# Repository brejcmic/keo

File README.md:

# B0B13KEO

- materiály, 
- prezentace

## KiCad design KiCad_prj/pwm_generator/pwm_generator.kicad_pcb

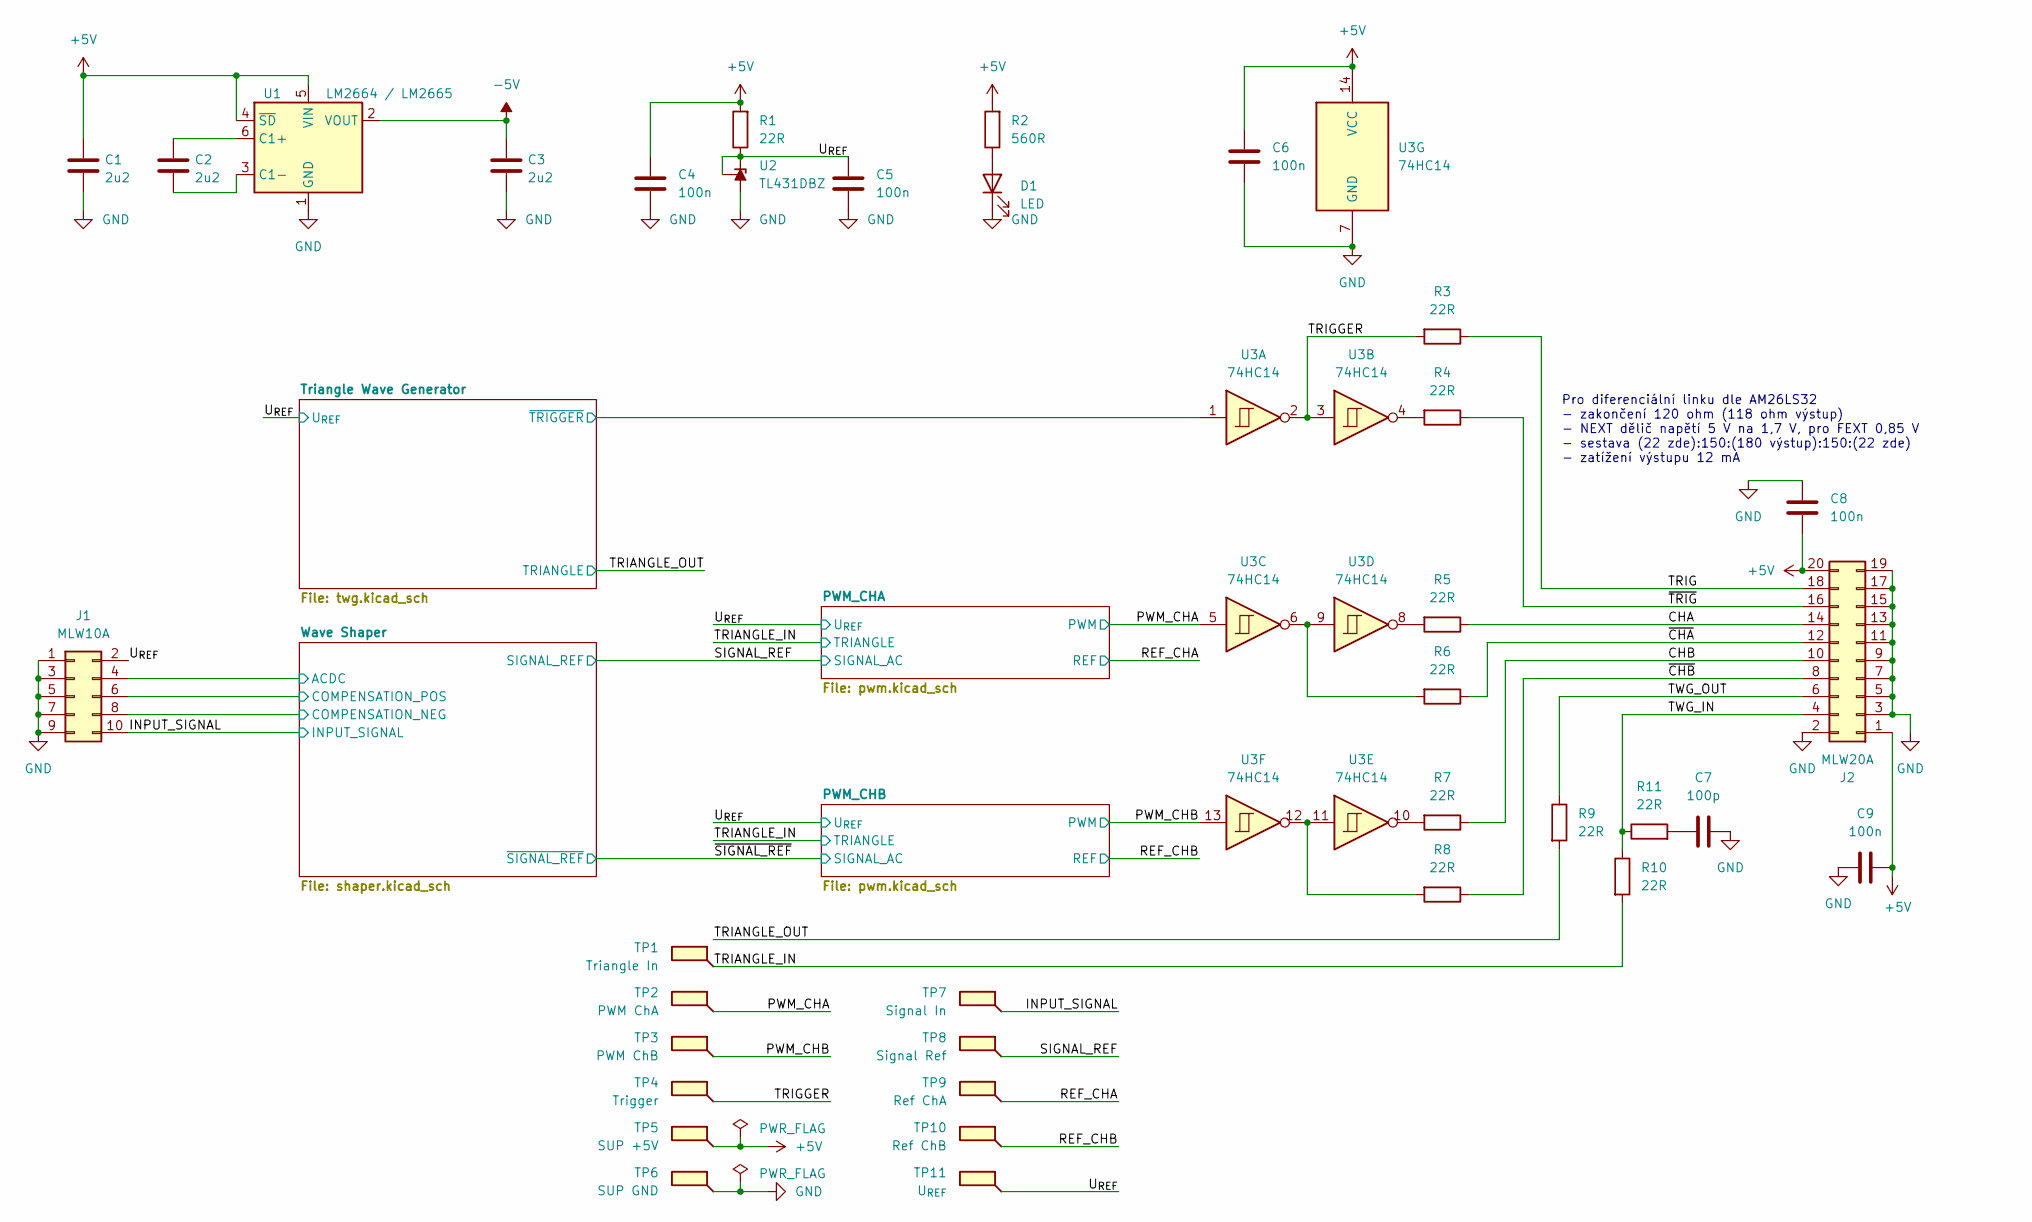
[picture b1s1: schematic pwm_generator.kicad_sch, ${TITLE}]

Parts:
C1, C2, C3: 2u2; C_0805_2012Metric; JLCPCB Part # C377773
C4, C5, C6, C8, C9: 100n; C_0805_2012Metric; JLCPCB Part # C49678
C7: 100p; C_0805_2012Metric; JLCPCB Part # C1790
D1: LED; LED_0805_2012Metric; JLCPCB Part # C84256
J1: MLW10A; IDC-Header_2x05_P2.54mm_Horizontal
J2: MLW20A; IDC-Header_2x10_P2.54mm_Horizontal
R1, R3, R4, R5, R6, R7, R8, R9, R10, R11: 22R; R_0805_2012Metric; JLCPCB Part # C17561
R2: 560R; R_0805_2012Metric; JLCPCB Part # C28636
TP1: Triangle In; TestPoint_Loop_D1.80mm_Drill1.0mm_Beaded
TP2: PWM ChA; TestPoint_Loop_D1.80mm_Drill1.0mm_Beaded
TP3: PWM ChB; TestPoint_Loop_D1.80mm_Drill1.0mm_Beaded
TP4: Trigger; TestPoint_Loop_D1.80mm_Drill1.0mm_Beaded
TP5: SUP +5V; TestPoint_Loop_D1.80mm_Drill1.0mm_Beaded
TP6: SUP GND; TestPoint_Loop_D1.80mm_Drill1.0mm_Beaded
TP7: Signal In; TestPoint_Loop_D1.80mm_Drill1.0mm_Beaded
TP8: Signal Ref; TestPoint_Loop_D1.80mm_Drill1.0mm_Beaded
TP9: Ref ChA; TestPoint_Loop_D1.80mm_Drill1.0mm_Beaded
TP10: Ref ChB; TestPoint_Loop_D1.80mm_Drill1.0mm_Beaded
TP11: U_{REF}; TestPoint_Loop_D1.80mm_Drill1.0mm_Beaded
U1: LM2664 / LM2665; SOT-23-6; JLCPCB Part # C840095
U2: TL431DBZ; SOT-23; JLCPCB Part # C181103
U3: 74HC14; SOIC-14_3.9x8.7mm_P1.27mm; JLCPCB Part # C5605

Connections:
+5V: C1.1, C4.2, C6.2, C8.2, C9.2, J2.1, J2.20, R1.2, R2.2, TP5.1 (1_1), U1.4 (~SD), U1.5 (VIN), U3.14 (VCC); also elsewhere on the board
-5V: C3.1, U1.2 (VOUT); also elsewhere on the board
/CHA: J2.14, R5.1
/CHB: J2.10, R7.1
/INPUT_SIGNAL: J1.10, TP7.1 (1_1); also elsewhere on the board
/PWM_CHA: TP2.1 (1_1), U3.5; also elsewhere on the board
/PWM_CHB: TP3.1 (1_1), U3.13; also elsewhere on the board
/REF_CHA: TP9.1 (1_1); also elsewhere on the board
/REF_CHB: TP10.1 (1_1); also elsewhere on the board
/SIGNAL_REF: TP8.1 (1_1); also elsewhere on the board
/TRIANGLE_IN: R10.2, TP1.1 (1_1); also elsewhere on the board
/TRIANGLE_OUT: R9.2; also elsewhere on the board
/TRIG: J2.18, R3.1
/TRIGGER: R3.2, TP4.1 (1_1), U3.2, U3.3
/TWG_IN: J2.4, R10.1, R11.1
/TWG_OUT: J2.6, R9.1
/Triangle Wave Generator/~TRIGGER: U3.1; also elsewhere on the board
/U_{REF}: C5.2, J1.2, R1.1, TP11.1 (1_1), U2.1 (K), U2.2 (REF); also elsewhere on the board
/Wave Shaper/ACDC: J1.4; also elsewhere on the board
/Wave Shaper/COMPENSATION_NEG: J1.8; also elsewhere on the board
/Wave Shaper/COMPENSATION_POS: J1.6; also elsewhere on the board
/~CHA: J2.12, R6.1
/~CHB: J2.8, R8.1
/~TRIG: J2.16, R4.1
GND: C1.2, C3.2, C4.1, C5.1, C6.1, C7.2, C8.1, C9.1, D1.1 (K), J1.1, J1.3, J1.5, J1.7, J1.9, J2.2, J2.3, J2.5, J2.7, J2.9, J2.11, J2.13, J2.15, J2.17, J2.19, TP6.1 (1_1), U1.1 (GND), U2.3 (A), U3.7 (GND); also elsewhere on the board
unnamed: C7.1, R11.2
unnamed: D1.2 (A), R2.1
unnamed: R4.2, U3.4
unnamed: R5.2, U3.8
unnamed: R6.2, U3.6, U3.9
unnamed: R7.2, U3.10
unnamed: R8.2, U3.11, U3.12
unnamed: C2.1, U1.6 (C1+)
unnamed: C2.2, U1.3 (C1-)

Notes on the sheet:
Pro diferenciální linku dle AM26LS32 - zakončení 120 ohm (118 ohm výstup) - NEXT dělič napětí 5 V na 1,7 V, pro FEXT 0,85 V - sestava (22 zde):150:(180 výstup):150:(22 zde) - zatížení výstupu 12 mA

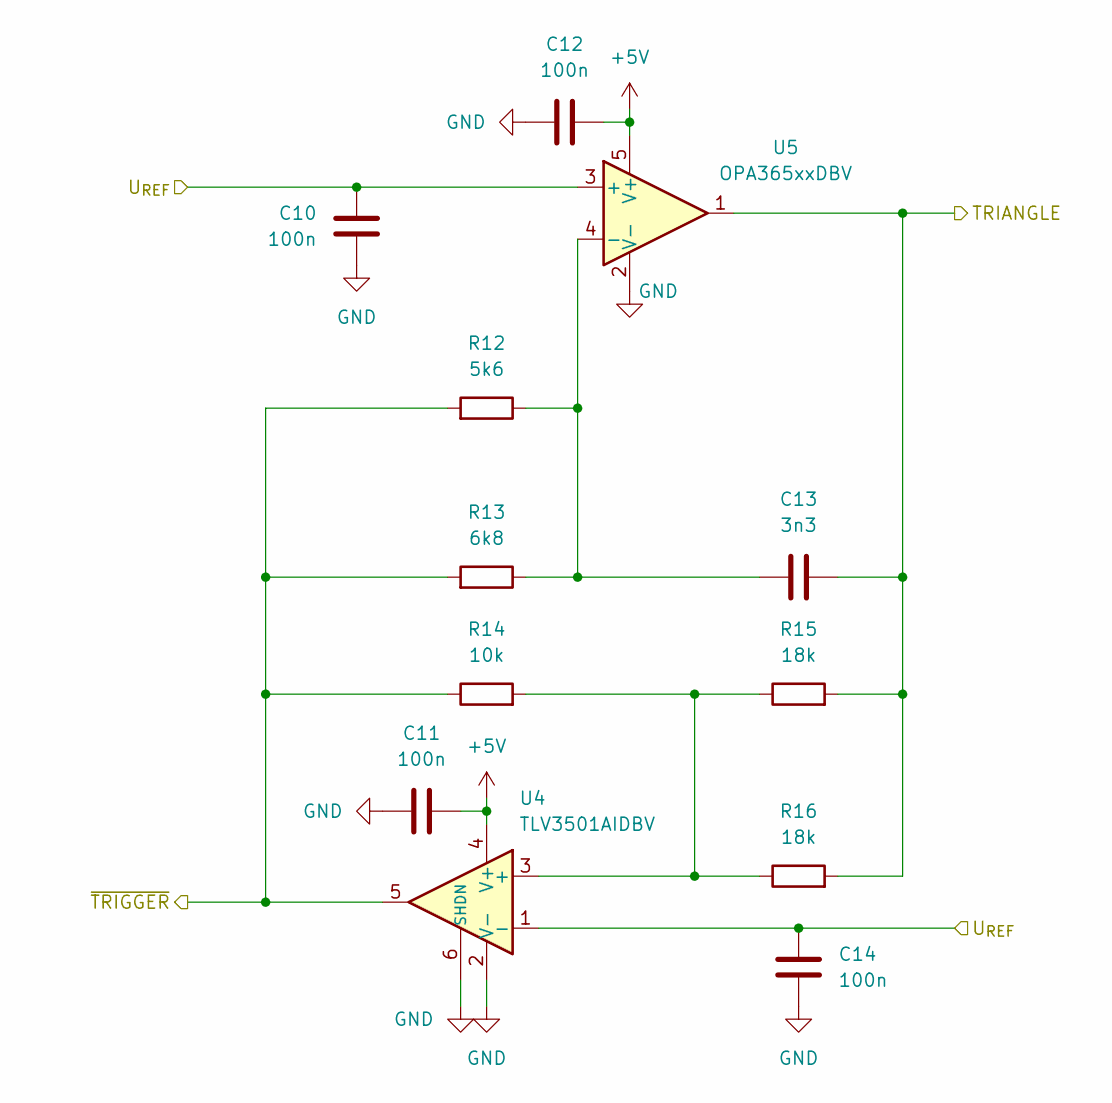
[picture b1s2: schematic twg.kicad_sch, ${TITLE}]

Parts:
C10, C11, C12, C14: 100n; C_0805_2012Metric; JLCPCB Part # C49678
C13: 3n3; C_0805_2012Metric; JLCPCB Part # C7467177
R12: 5k6; R_0805_2012Metric; JLCPCB Part # C4382
R13: 6k8; R_0805_2012Metric; JLCPCB Part # C17772
R14: 10k; R_0805_2012Metric; JLCPCB Part # C17414
R15, R16: 18k; R_0805_2012Metric; JLCPCB Part # C17506
U4: TLV3501AIDBV; SOT-23-6; JLCPCB Part # C193413
U5: OPA365xxDBV; SOT-23-5; JLCPCB Part # C96626

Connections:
+5V: C11.2, C12.2, U4.4 (V+), U5.5 (V+); also elsewhere on the board
/TRIANGLE_OUT: C13.2, R15.2, R16.2, U5.1; also elsewhere on the board
/Triangle Wave Generator/~TRIGGER: R12.2, R13.2, R14.1, U4.5; also elsewhere on the board
/U_{REF}: C10.2, C14.2, U4.1 (-), U5.3 (+); also elsewhere on the board
GND: C10.1, C11.1, C12.1, C14.1, U4.2 (V-), U4.6 (SHDN), U5.2 (V-); also elsewhere on the board
unnamed: R14.2, R15.1, R16.1, U4.3 (+)
unnamed: C13.1, R12.1, R13.1, U5.4 (-)

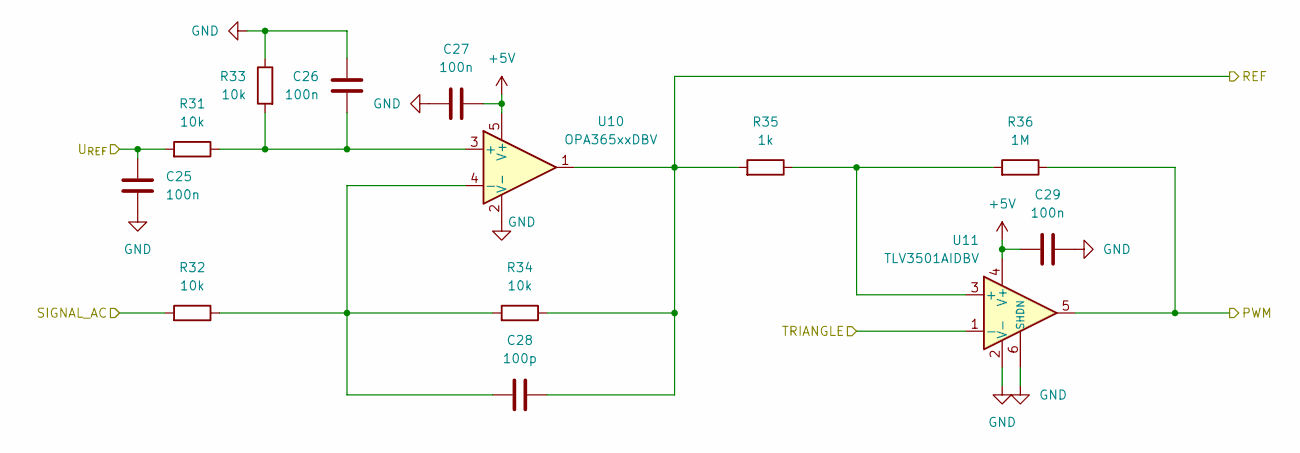
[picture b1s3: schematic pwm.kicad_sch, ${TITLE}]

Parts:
C25, C26, C27, C29: 100n; C_0805_2012Metric; JLCPCB Part # C49678
C28: 100p; C_0805_2012Metric; JLCPCB Part # C1790
R31, R32, R33, R34: 10k; R_0805_2012Metric; JLCPCB Part # C17414
R35: 1k; R_0805_2012Metric; JLCPCB Part # C17513
R36: 1M; R_0805_2012Metric; JLCPCB Part # C17514
U10: OPA365xxDBV; SOT-23-5; JLCPCB Part # C96626
U11: TLV3501AIDBV; SOT-23-6; JLCPCB Part # C193413

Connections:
+5V: C27.2, C29.2, U10.5 (V+), U11.4 (V+); also elsewhere on the board
/PWM_CHA: R36.1, U11.5; also elsewhere on the board
/REF_CHA: C28.2, R34.1, R35.2, U10.1; also elsewhere on the board
/SIGNAL_REF: R32.2; also elsewhere on the board
/TRIANGLE_IN: U11.1 (-); also elsewhere on the board
/U_{REF}: C25.2, R31.2; also elsewhere on the board
GND: C25.1, C26.1, C27.1, C29.1, R33.1, U10.2 (V-), U11.2 (V-), U11.6 (SHDN); also elsewhere on the board
unnamed: C26.2, R31.1, R33.2, U10.3 (+)
unnamed: C28.1, R32.1, R34.2, U10.4 (-)
unnamed: R35.1, R36.2, U11.3 (+)

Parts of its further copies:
C30, C31, C32, C34: 100n; C_0805_2012Metric; JLCPCB Part # C49678
C33: 100p; C_0805_2012Metric; JLCPCB Part # C1790
R37, R38, R39, R40: 10k; R_0805_2012Metric; JLCPCB Part # C17414
R41: 1k; R_0805_2012Metric; JLCPCB Part # C17513
R42: 1M; R_0805_2012Metric; JLCPCB Part # C17514
U12: OPA365xxDBV; SOT-23-5; JLCPCB Part # C96626
U13: TLV3501AIDBV; SOT-23-6; JLCPCB Part # C193413

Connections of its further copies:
+5V: C32.2, C34.2, U12.5 (V+), U13.4 (V+); also elsewhere on the board
/PWM_CHB: R42.1, U13.5; also elsewhere on the board
/REF_CHB: C33.2, R40.1, R41.2, U12.1; also elsewhere on the board
/TRIANGLE_IN: U13.1 (-); also elsewhere on the board
/U_{REF}: C30.2, R37.2; also elsewhere on the board
/~SIGNAL_REF: R38.2; also elsewhere on the board
GND: C30.1, C31.1, C32.1, C34.1, R39.1, U12.2 (V-), U13.2 (V-), U13.6 (SHDN); also elsewhere on the board
unnamed: C31.2, R37.1, R39.2, U12.3 (+)
unnamed: C33.1, R38.1, R40.2, U12.4 (-)
unnamed: R41.1, R42.2, U13.3 (+)

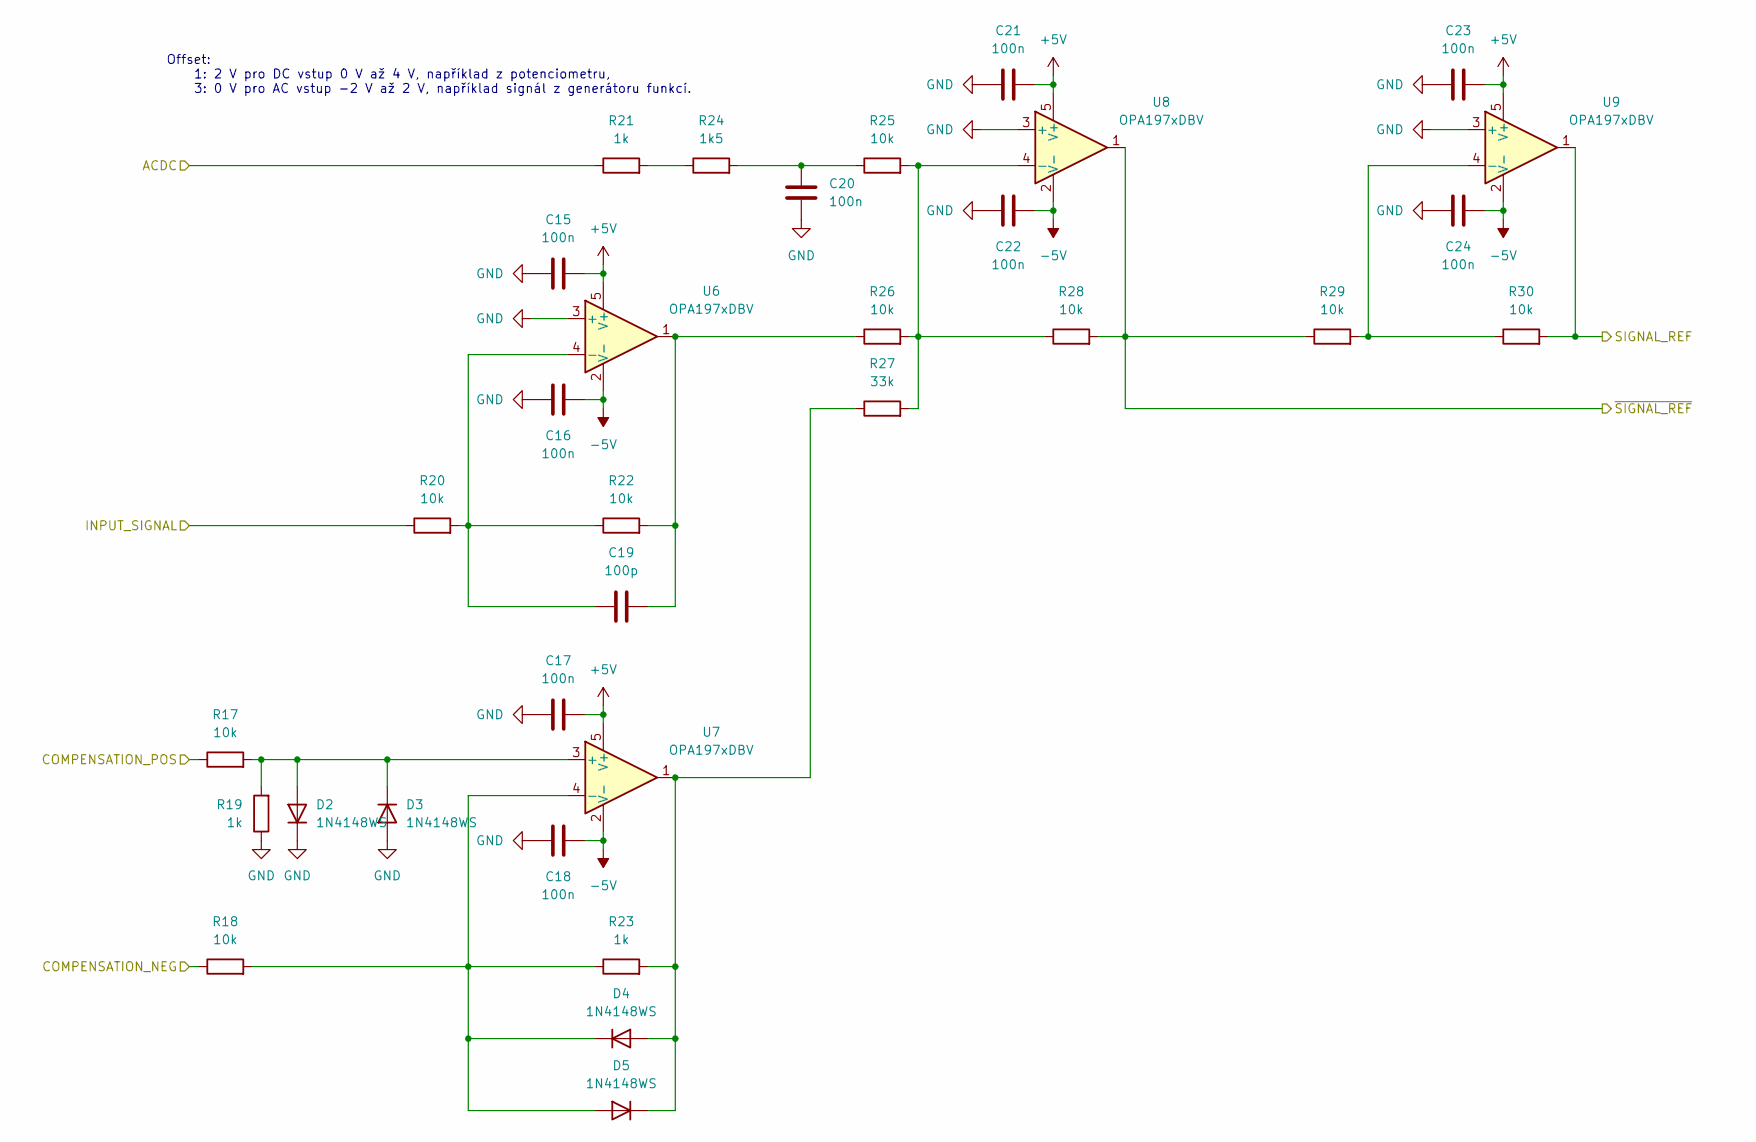
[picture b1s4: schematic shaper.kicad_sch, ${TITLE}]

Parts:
C15, C16, C17, C18, C20, C21, C22, C23, C24: 100n; C_0805_2012Metric; JLCPCB Part # C49678
C19: 100p; C_0805_2012Metric; JLCPCB Part # C1790
D2, D3, D4, D5: 1N4148WS; D_SOD-323; JLCPCB Part # C2128
R17, R18, R20, R22, R25, R26, R28, R29, R30: 10k; R_0805_2012Metric; JLCPCB Part # C17414
R19, R21, R23: 1k; R_0805_2012Metric; JLCPCB Part # C17513
R24: 1k5; R_0805_2012Metric; JLCPCB Part # C4310
R27: 33k; R_0805_2012Metric; JLCPCB Part # C17633
U6, U7, U8, U9: OPA197xDBV; SOT-23-5; JLCPCB Part # C221351

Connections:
+5V: C15.2, C17.2, C21.2, C23.2, U6.5 (V+), U7.5 (V+), U8.5 (V+), U9.5 (V+); also elsewhere on the board
-5V: C16.2, C18.2, C22.2, C24.2, U6.2 (V-), U7.2 (V-), U8.2 (V-), U9.2 (V-); also elsewhere on the board
/INPUT_SIGNAL: R20.1; also elsewhere on the board
/SIGNAL_REF: R30.2, U9.1; also elsewhere on the board
/Wave Shaper/ACDC: R21.1; also elsewhere on the board
/Wave Shaper/COMPENSATION_NEG: R18.1; also elsewhere on the board
/Wave Shaper/COMPENSATION_POS: R17.1; also elsewhere on the board
/~SIGNAL_REF: R28.2, R29.1, U8.1; also elsewhere on the board
GND: C15.1, C16.1, C17.1, C18.1, C20.1, C21.1, C22.1, C23.1, C24.1, D2.1 (K), D3.2 (A), R19.1, U6.3 (+), U8.3 (+), U9.3 (+); also elsewhere on the board
unnamed: C19.2, R22.2, R26.1, U6.1
unnamed: C20.2, R24.2, R25.1
unnamed: D2.2 (A), D3.1 (K), R17.2, R19.2, U7.3 (+)
unnamed: D4.2 (A), D5.1 (K), R23.2, R27.1, U7.1
unnamed: D4.1 (K), D5.2 (A), R18.2, R23.1, U7.4 (-)
unnamed: R21.2, R24.1
unnamed: C19.1, R20.2, R22.1, U6.4 (-)
unnamed: R25.2, R26.2, R27.2, R28.1, U8.4 (-)
unnamed: R29.2, R30.1, U9.4 (-)

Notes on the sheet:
Offset: 1: 2 V pro DC vstup 0 V až 4 V, například z potenciometru, 3: 0 V pro AC vstup -2 V až 2 V, například signál z generátoru funkcí.

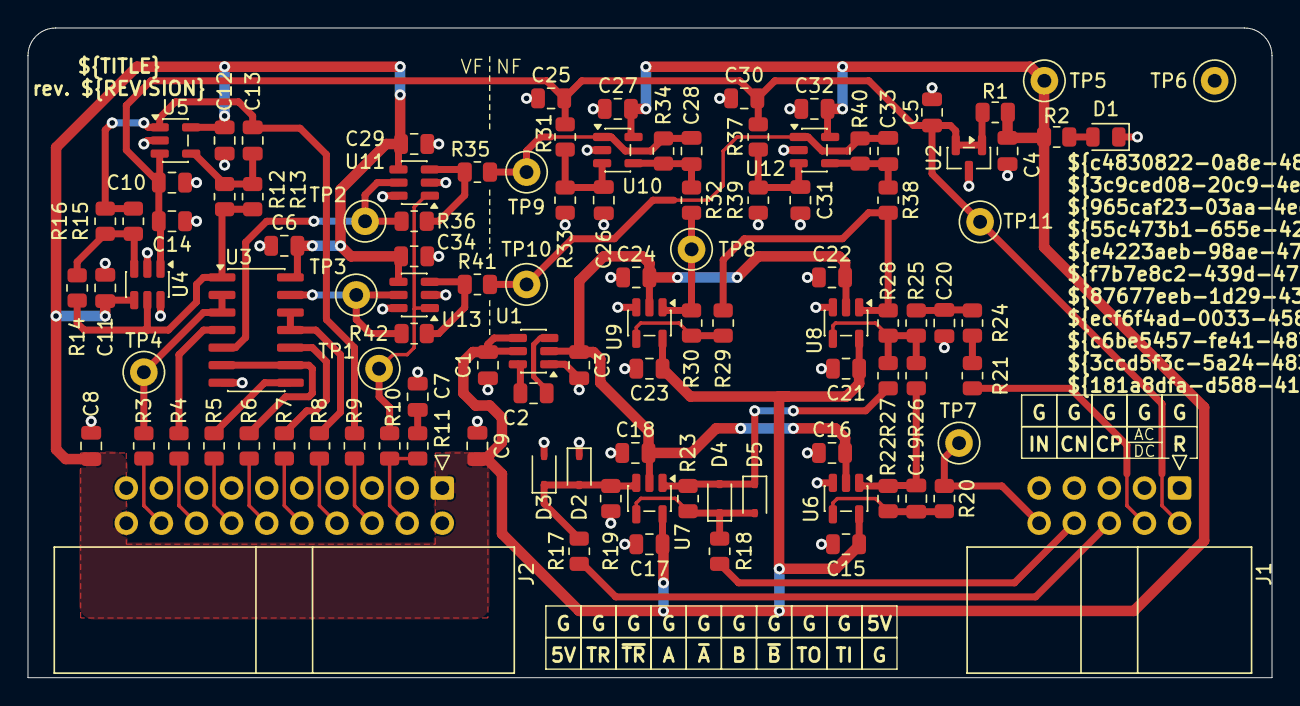
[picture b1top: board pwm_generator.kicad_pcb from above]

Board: 2 copper layers, 90.0 x 47.0 mm, 107 parts (0 on the bottom side), 52 nets.

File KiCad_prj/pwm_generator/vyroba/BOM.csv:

"Comment","Designator","Footprint","JLCPCB Part #"
"100p","C7,C19,C28,C33","Capacitor_SMD:C_0805_2012Metric","C1790"
"3n3","C13","Capacitor_SMD:C_0805_2012Metric","C7467177"
"100n","C4,C5,C6,C8,C9,C10,C11,C12,C14,C15,C16,C17,C18,C20,C21,C22,C23,C24,C25,C26,C27,C29,C30,C31,C32,C34","Capacitor_SMD:C_0805_2012Metric","C49678"
"2u2","C1,C2,C3","Capacitor_SMD:C_0805_2012Metric","C377773"
"22R","R3,R4,R5,R6,R7,R8,R9,R10,R11","Resistor_SMD:R_0805_2012Metric","C17561"
"560R","R1,R2","Resistor_SMD:R_0805_2012Metric","C28636"
"1k","R19,R21,R23,R35,R41","Resistor_SMD:R_0805_2012Metric","C17513"
"1k5","R24","Resistor_SMD:R_0805_2012Metric","C4310"
"5k6","R12","Resistor_SMD:R_0805_2012Metric","C4382"
"6k8","R13","Resistor_SMD:R_0805_2012Metric","C17772"
"10k","R14,R17,R18,R20,R22,R25,R26,R28,R29,R30,R31,R32,R33,R34,R37,R38,R39,R40","Resistor_SMD:R_0805_2012Metric","C17414"
"18k","R15,R16","Resistor_SMD:R_0805_2012Metric","C17506"
"33k","R27","Resistor_SMD:R_0805_2012Metric","C17633"
"1M","R36,R42","Resistor_SMD:R_0805_2012Metric","C17514"
"1N4148WS","D2,D3,D4,D5","Diode_SMD:D_SOD-323","C2128"
"74HC14","U3","Package_SO:SOIC-14_3.9x8.7mm_P1.27mm","C5605"
"BZT52C2V0","D6,D7","Diode_SMD:D_SOD-123F","C41410795"
"LED","D1","LED_SMD:LED_0805_2012Metric","C84256"
"LM2664 / LM2665","U1","Package_TO_SOT_SMD:SOT-23-6","C840095"
"OPA197xDBV","U6,U7,U8,U9","Package_TO_SOT_SMD:SOT-23-5","C221351"
"OPA365xxDBV","U5,U10,U12","Package_TO_SOT_SMD:SOT-23-5","C96626"
"TL431DBZ","U2","Package_TO_SOT_SMD:SOT-23","C181103"
"TLV3501AIDBV","U4,U11,U13","Package_TO_SOT_SMD:SOT-23-6","C193413"

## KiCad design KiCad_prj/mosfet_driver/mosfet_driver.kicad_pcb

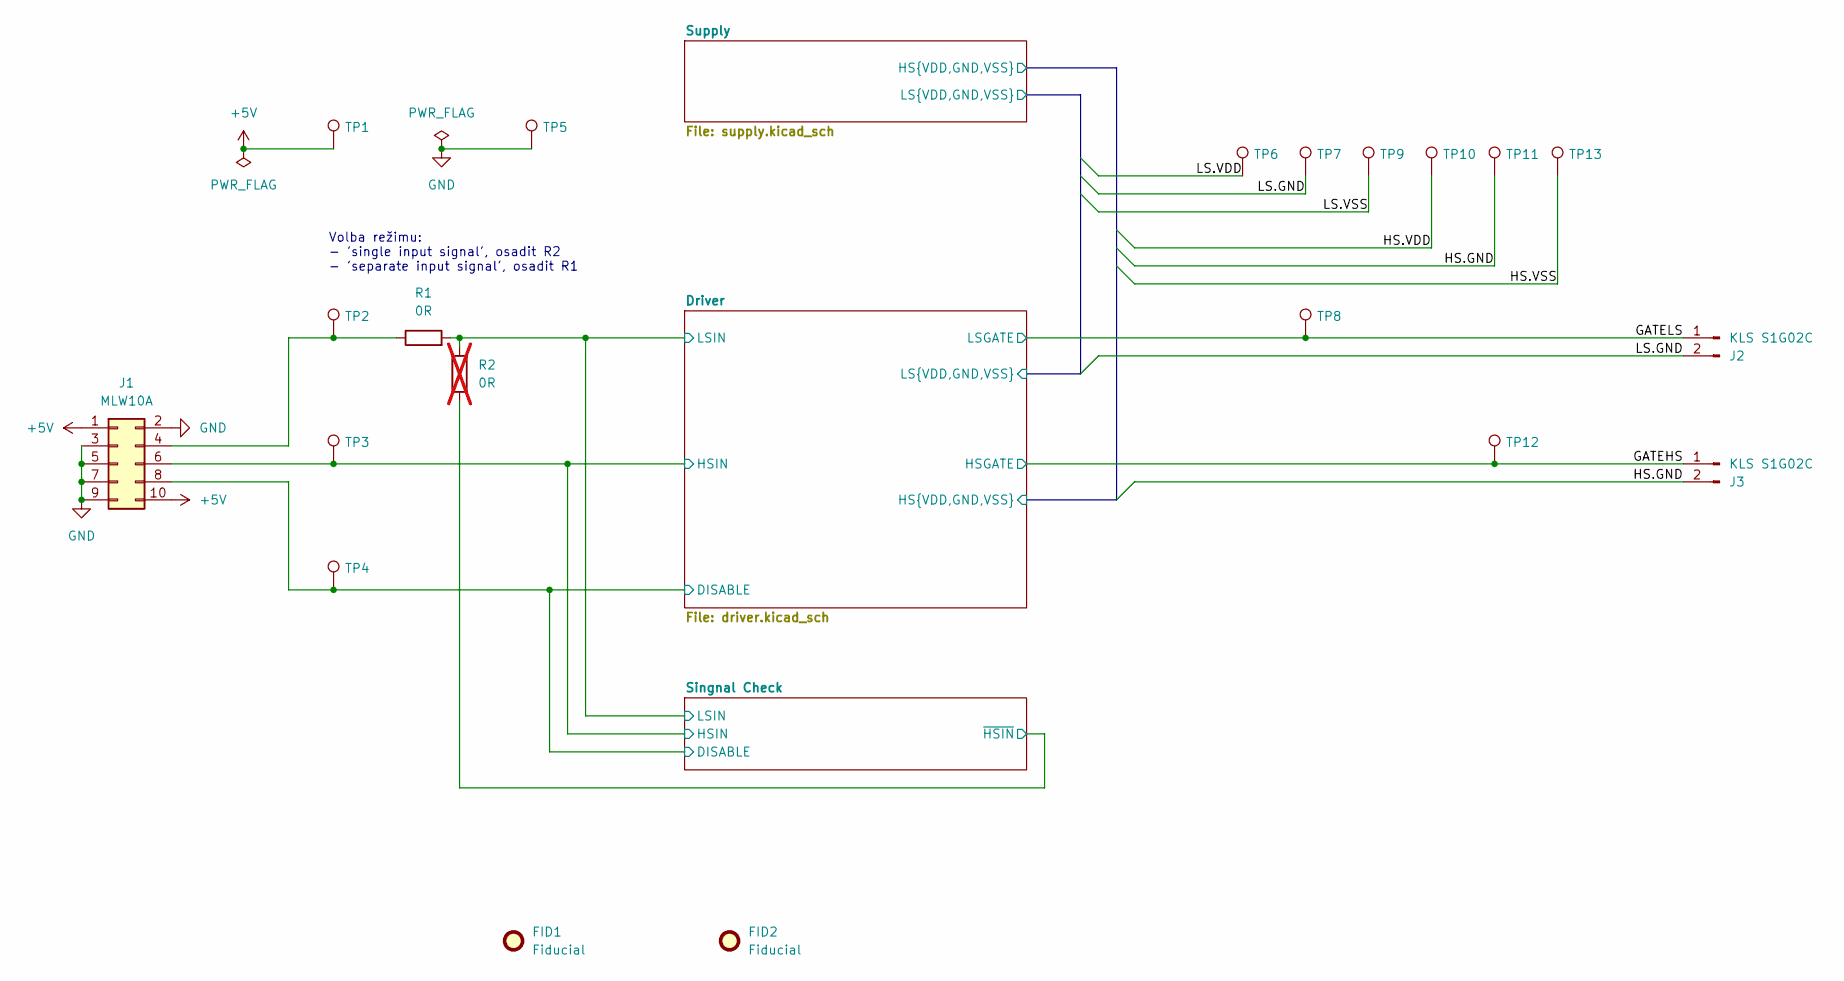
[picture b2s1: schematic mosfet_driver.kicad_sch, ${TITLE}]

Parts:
FID1, FID2: Fiducial; Fiducial_0.5mm_Mask1mm
J1: MLW10A; IDC-Header_2x05_P2.54mm_Horizontal
J2, J3: KLS S1G02C; PinHeader_1x02_P2.54mm_Horizontal
R1: 0R; R_0805_2012Metric; JLCPCB Part # C17477
R2: 0R; R_0805_2012Metric; JLCPCB Part # C17477; not fitted
TP1, TP2, TP3, TP4, TP5, TP6, TP7, TP8, TP9, TP10, TP11, TP12, TP13: D1MM; TestPoint_Loop_D2.50mm_Drill1.0mm

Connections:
+5V: J1.1, J1.10, TP1.1 (1_1); also elsewhere on the board
/Driver/DISABLE: J1.8, TP4.1 (1_1); also elsewhere on the board
/Driver/HS.GND: J3.2, TP11.1 (1_1); also elsewhere on the board
/Driver/HS.VDD: TP10.1 (1_1); also elsewhere on the board
/Driver/HS.VSS: TP13.1 (1_1); also elsewhere on the board
/Driver/HSIN: J1.6, TP3.1 (1_1); also elsewhere on the board
/Driver/LS.GND: J2.2, TP7.1 (1_1); also elsewhere on the board
/Driver/LS.VDD: TP6.1 (1_1); also elsewhere on the board
/Driver/LS.VSS: TP9.1 (1_1); also elsewhere on the board
/Driver/LSIN: R1.2, R2.1; also elsewhere on the board
/GATEHS: J3.1, TP12.1 (1_1); also elsewhere on the board
/GATELS: J2.1, TP8.1 (1_1); also elsewhere on the board
/Singnal Check/~HSIN: R2.2; also elsewhere on the board
GND: J1.2, J1.3, J1.5, J1.7, J1.9, TP5.1 (1_1); also elsewhere on the board
unnamed: J1.4, R1.1, TP2.1 (1_1)

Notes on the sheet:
Volba režimu: - 'single input signal', osadit R2 - 'separate input signal', osadit R1

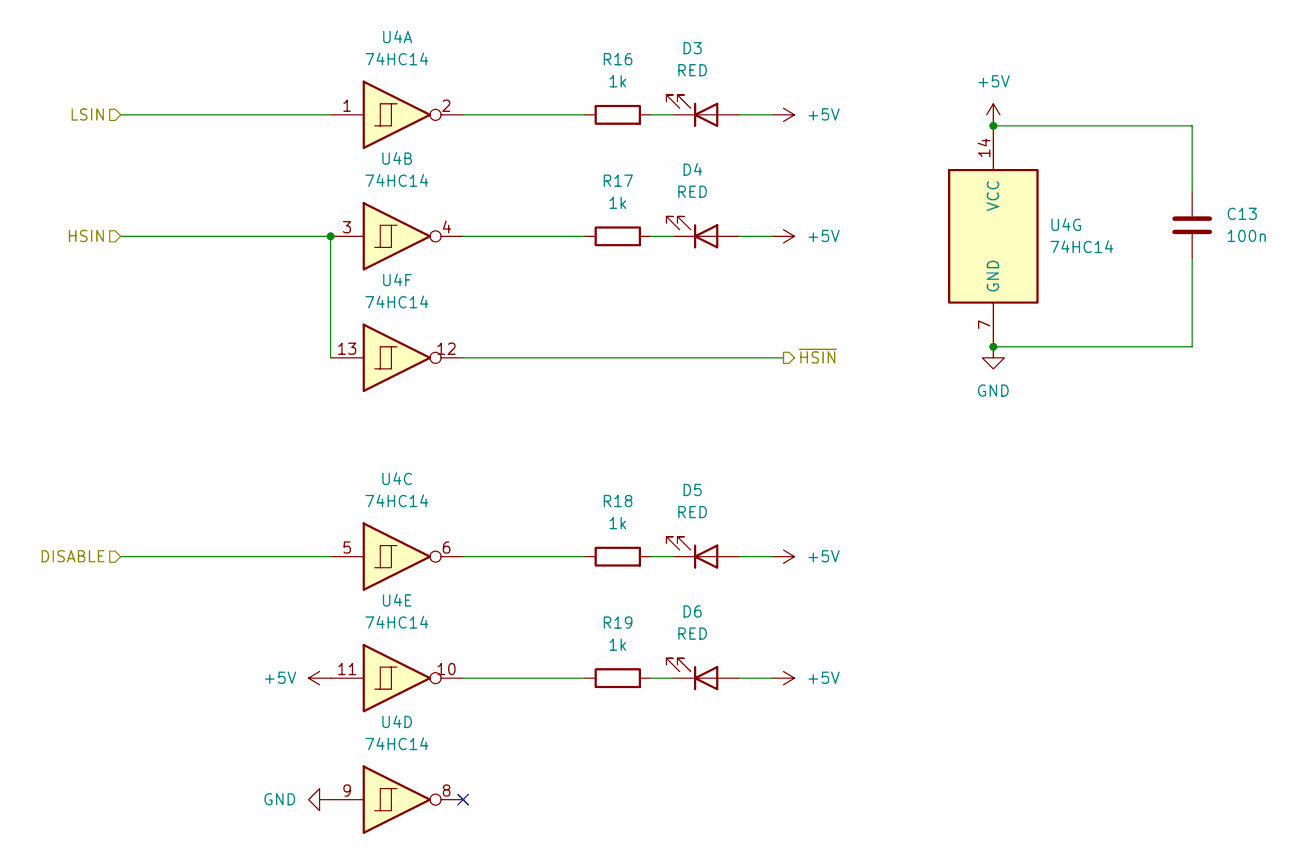
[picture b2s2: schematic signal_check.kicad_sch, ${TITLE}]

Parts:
C13: 100n; C_0805_2012Metric; JLCPCB Part # C28233
D3, D4, D5, D6: RED; LED_0805_2012Metric; JLCPCB Part # C84256
R16, R17, R18, R19: 1k; R_0805_2012Metric; JLCPCB Part # C17513
U4: 74HC14; SOIC-14_3.9x8.7mm_P1.27mm; JLCPCB Part # C5605

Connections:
+5V: C13.1, D3.2 (A), D4.2 (A), D5.2 (A), D6.2 (A), U4.11, U4.14 (VCC); also elsewhere on the board
/Driver/DISABLE: U4.5; also elsewhere on the board
/Driver/HSIN: U4.3, U4.13; also elsewhere on the board
/Driver/LSIN: U4.1; also elsewhere on the board
/Singnal Check/~HSIN: U4.12; also elsewhere on the board
GND: C13.2, U4.7 (GND), U4.9; also elsewhere on the board
unnamed: D3.1 (K), R16.2
unnamed: D4.1 (K), R17.2
unnamed: D5.1 (K), R18.2
unnamed: D6.1 (K), R19.2
unnamed: R16.1, U4.2
unnamed: R17.1, U4.4
unnamed: R18.1, U4.6
unnamed: R19.1, U4.10

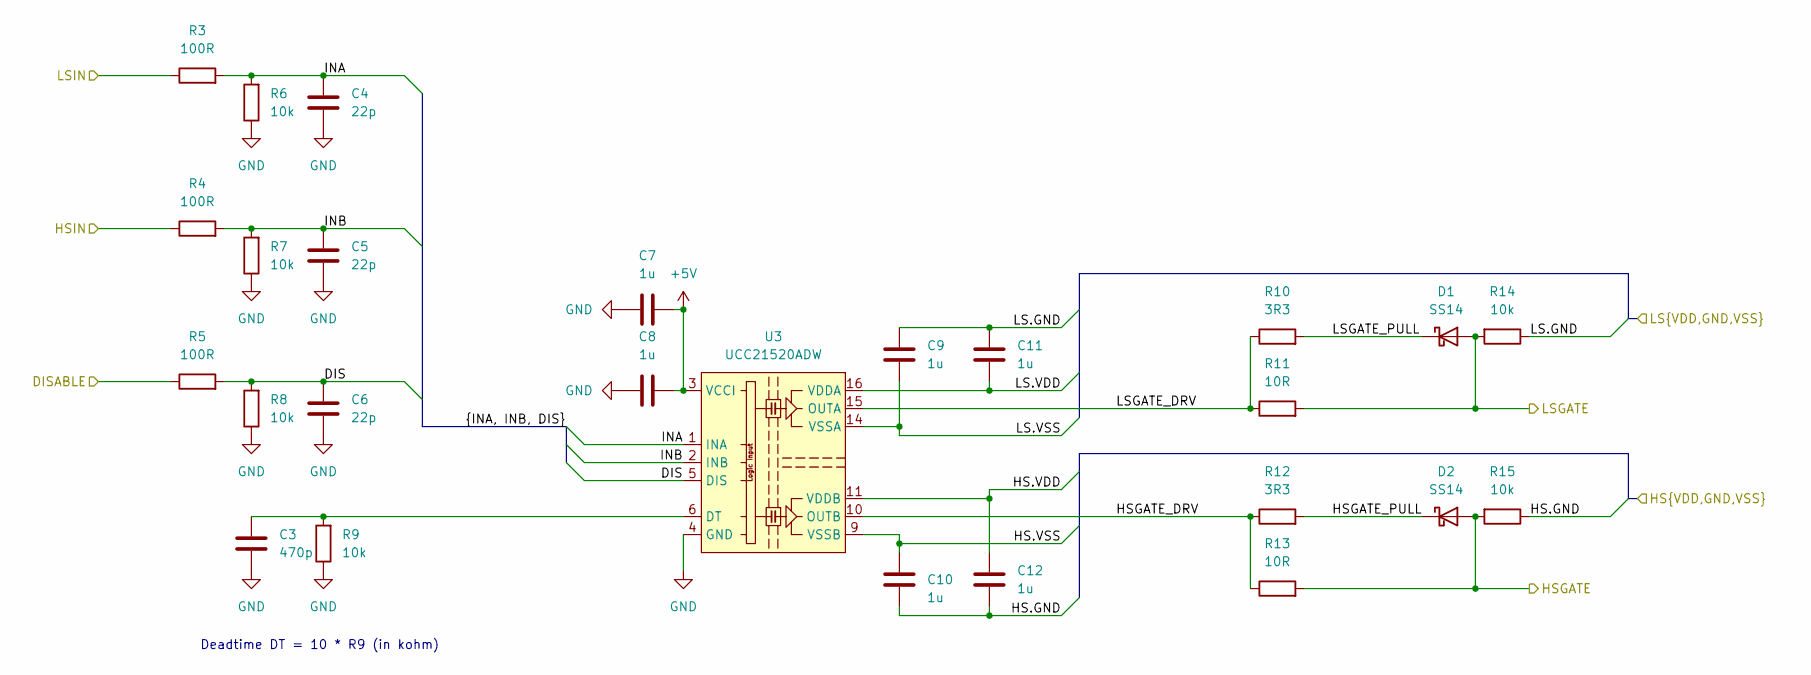
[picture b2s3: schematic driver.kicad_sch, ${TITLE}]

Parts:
C3: 470p; C_0805_2012Metric; JLCPCB Part # C1743
C4, C5, C6: 22p; C_0805_2012Metric; JLCPCB Part # C1804
C7, C8, C9, C10, C11, C12: 1u; C_0805_2012Metric; JLCPCB Part # C28323
D1, D2: SS14; D_SMA; JLCPCB Part # C2480
R3, R4, R5: 100R; R_0805_2012Metric; JLCPCB Part # C17408
R6, R7, R8, R9, R14, R15: 10k; R_0805_2012Metric; JLCPCB Part # C17414
R10, R12: 3R3; R_0805_2012Metric; JLCPCB Part # C16257
R11, R13: 10R; R_0805_2012Metric; JLCPCB Part # C17415
U3: UCC21520ADW; SOIC-16W_7.5x10.3mm_P1.27mm; JLCPCB Part # C2863027

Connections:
+5V: C7.1, C8.1, U3.3 (VCCI), U3.8 (VCCI); also elsewhere on the board
/Driver/DIS: C6.1, R5.2, R8.2, U3.5 (DIS)
/Driver/DISABLE: R5.1; also elsewhere on the board
/Driver/HS.GND: C10.2, C12.2, R15.1; also elsewhere on the board
/Driver/HS.VDD: C12.1, U3.11 (VDDB); also elsewhere on the board
/Driver/HS.VSS: C10.1, U3.9 (VSSB); also elsewhere on the board
/Driver/HSGATE_DRV: R12.1, R13.1, U3.10 (OUTB)
/Driver/HSGATE_PULL: D2.1 (K), R12.2
/Driver/HSIN: R4.1; also elsewhere on the board
/Driver/INA: C4.1, R3.2, R6.2, U3.1 (INA)
/Driver/INB: C5.1, R4.2, R7.2, U3.2 (INB)
/Driver/LS.GND: C9.2, C11.2, R14.1; also elsewhere on the board
/Driver/LS.VDD: C11.1, U3.16 (VDDA); also elsewhere on the board
/Driver/LS.VSS: C9.1, U3.14 (VSSA); also elsewhere on the board
/Driver/LSGATE_DRV: R10.1, R11.1, U3.15 (OUTA)
/Driver/LSGATE_PULL: D1.1 (K), R10.2
/Driver/LSIN: R3.1; also elsewhere on the board
/GATEHS: D2.2 (A), R13.2, R15.2; also elsewhere on the board
/GATELS: D1.2 (A), R11.2, R14.2; also elsewhere on the board
GND: C3.2, C4.2, C5.2, C6.2, C7.2, C8.2, R6.1, R7.1, R8.1, R9.1, U3.4 (GND); also elsewhere on the board
unnamed: C3.1, R9.2, U3.6 (DT)

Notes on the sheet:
Deadtime DT = 10 * R9 (in kohm)

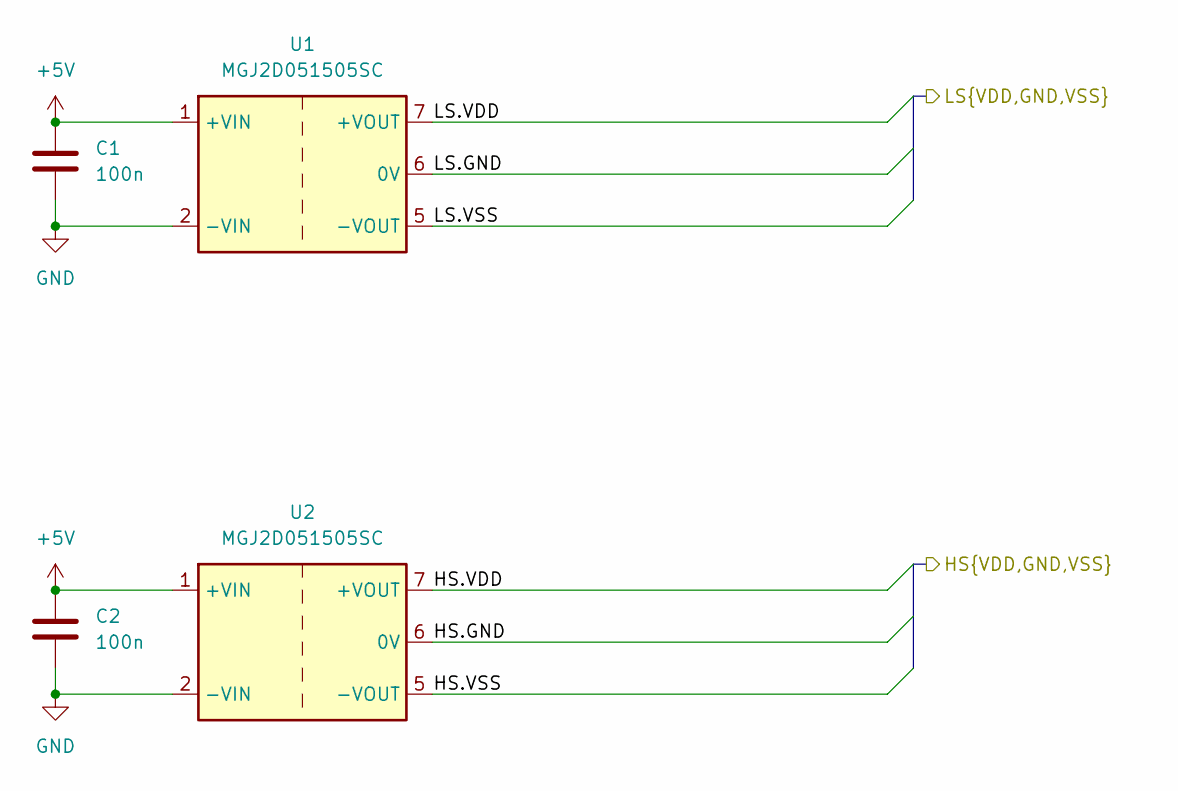
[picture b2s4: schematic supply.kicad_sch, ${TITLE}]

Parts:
C1, C2: 100n; C_0805_2012Metric; JLCPCB Part # C28233
U1, U2: MGJ2D051505SC; Converter_DCDC_Murata_MGJ2DxxxxxxSC_THT

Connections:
+5V: C1.2, C2.2, U1.1 (+VIN), U2.1 (+VIN); also elsewhere on the board
/Driver/HS.GND: U2.6 (0V); also elsewhere on the board
/Driver/HS.VDD: U2.7 (+VOUT); also elsewhere on the board
/Driver/HS.VSS: U2.5 (-VOUT); also elsewhere on the board
/Driver/LS.GND: U1.6 (0V); also elsewhere on the board
/Driver/LS.VDD: U1.7 (+VOUT); also elsewhere on the board
/Driver/LS.VSS: U1.5 (-VOUT); also elsewhere on the board
GND: C1.1, C2.1, U1.2 (-VIN), U2.2 (-VIN); also elsewhere on the board
